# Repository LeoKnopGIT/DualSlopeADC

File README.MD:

# DualSlopeADC

Ein 12-Bit-Dual-Slope-ADC mit CH32V003 Mikrocontroller und 4-stelligem 7-Segment-Display zur Anzeige der gemessenen Gleichspannung.

## 🔧 Projektüberblick

Dieses Projekt implementiert einen Dual-Slope-Analog-Digital-Wandler (ADC), wie er z. B. in Digitalmultimetern zum Einsatz kommt. Die Schaltung misst Eingangsspannungen im Bereich von 0–3.3 V und visualisiert das Ergebnis auf einem 7-Segment-Display.

## ⚙️ Hardware

| Komponente       | Beschreibung                  |
|------------------|-------------------------------|
| Mikrocontroller  | CH32V003 (RISC-V, 48 MHz)     |
| Anzeige          | 4-stelliges 7-Segment-Display |
| Betriebsspannung | 3.3 V                         |
| Auflösung        | 12 Bit (theoretisch)          |
| Zeitauflösung    | ~20 ns (Timer mit 48 MHz)     |

## 📐 Funktionsweise

### ⏱ Prinzip: Dual-Slope-Wandlung

1. **Integration (Messphase):**  
   Eingangsspannung wird über ein RC-Glied integriert  
   → Spannungsanstieg proportional zu \( V_{in} - V_{off} \)

2. **Gegenintegration (Referenzphase):**  
   Eine konstante Referenzspannung wird integriert, bis der Ausgang wieder 0 V erreicht.

3. **Zeitmessung:**  
   Die Dauer dieser Rücklaufphase ist proportional zur Eingangsspannung.

### Simulation

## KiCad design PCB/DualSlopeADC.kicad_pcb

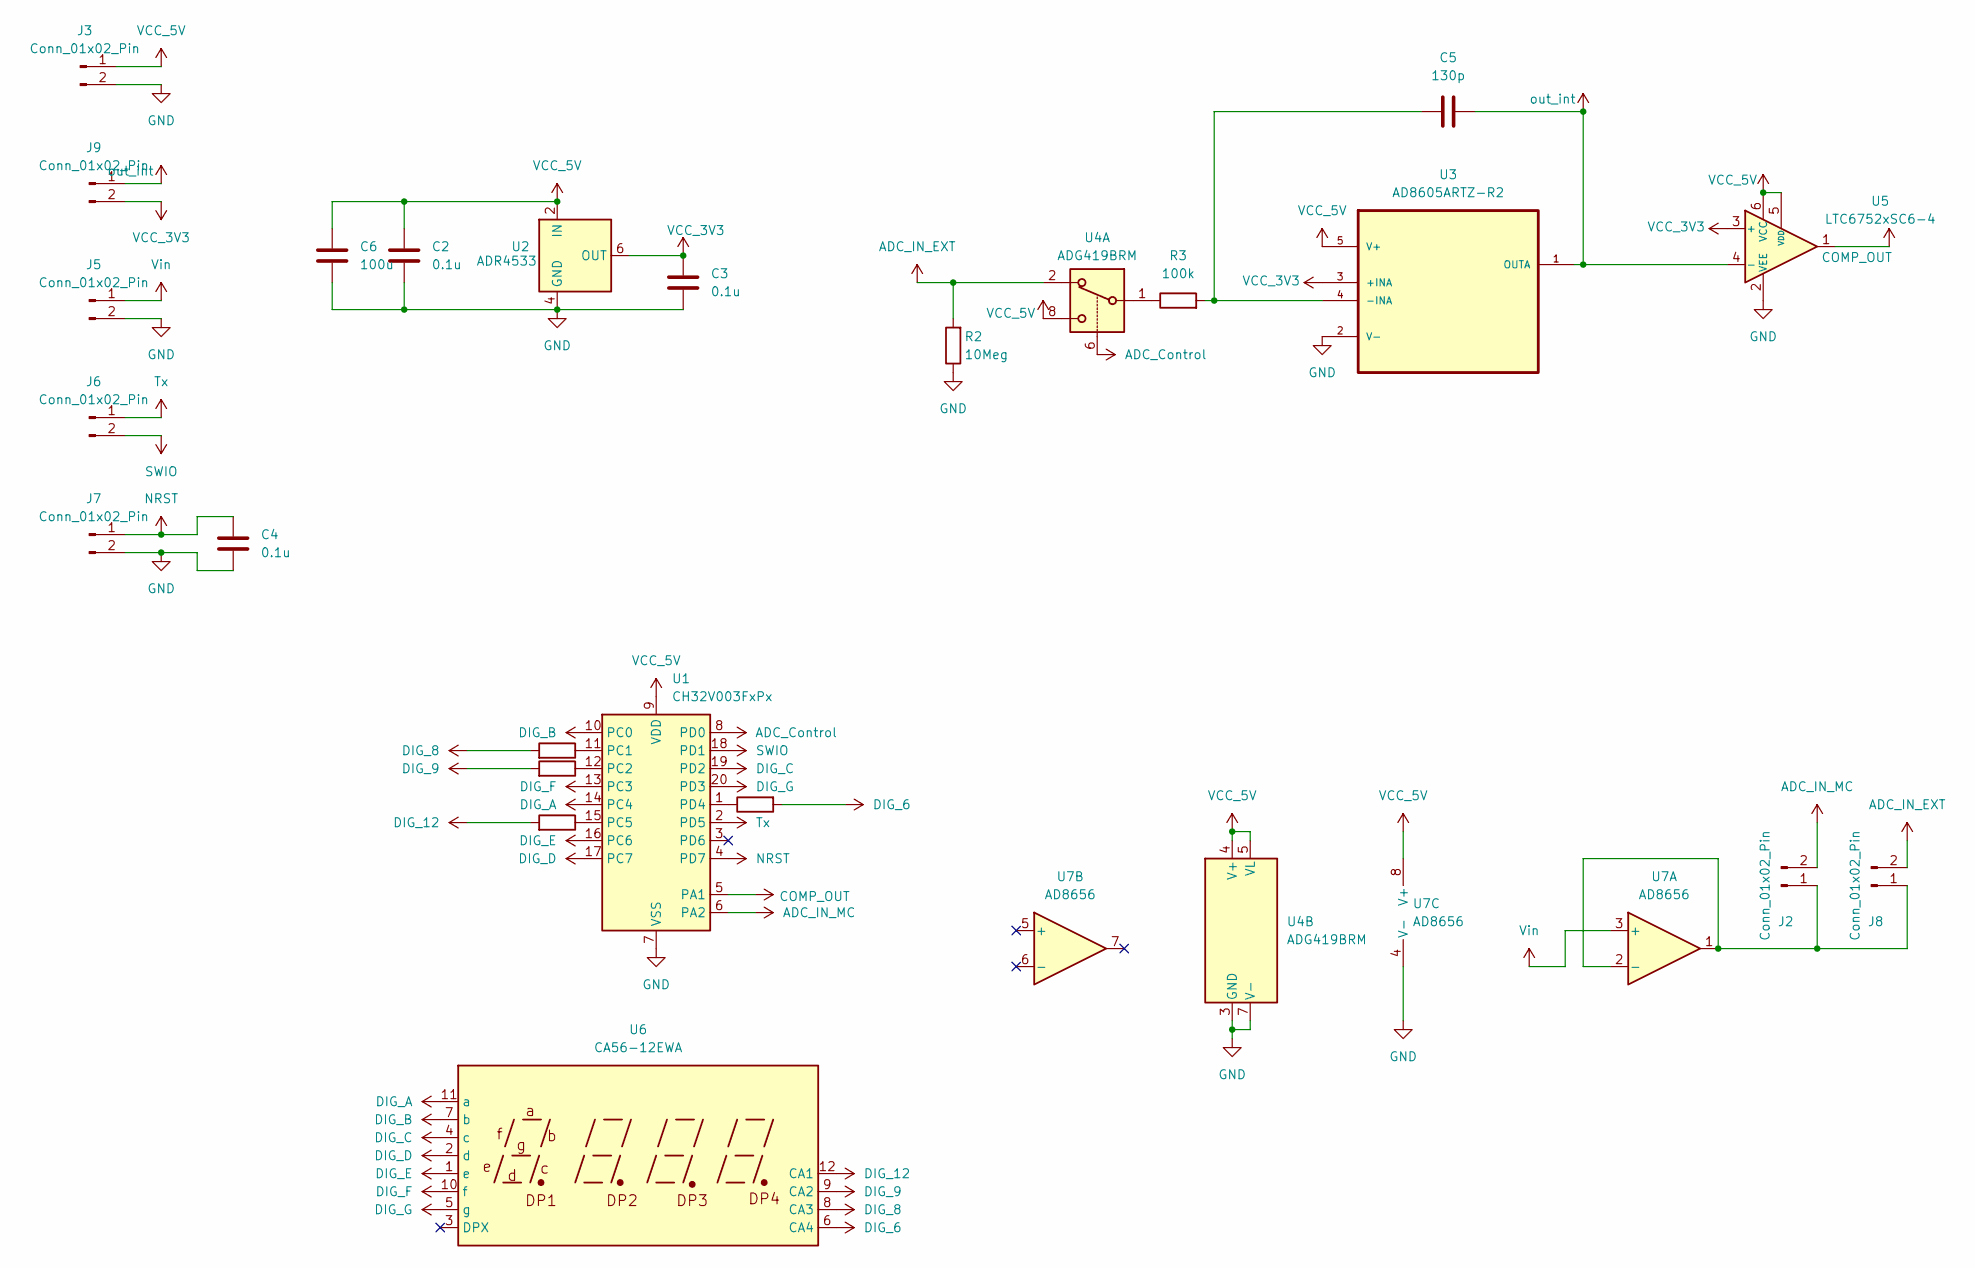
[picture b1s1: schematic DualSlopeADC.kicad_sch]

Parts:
C2, C3, C4: 0.1u; C_0805_2012Metric
C5: 130p; C_0805_2012Metric
C6: 100u; CP_Radial_D12.5mm_P5.00mm
J2, J3, J5, J6, J7, J8, J9: Conn_01x02_Pin; PinHeader_1x02_P2.54mm_Vertical
R2: 10Meg; R_0603_1608Metric
R3: 100k; R_0603_1608Metric
R4, R5, R6, R7: 330; R_0603_1608Metric
U1: CH32V003FxPx; TSSOP-20_4.4x6.5mm_P0.65mm
U2: ADR4533; SOIC-8_3.9x4.9mm_P1.27mm
U3: AD8605ARTZ-R2; SOT95P290X145-5N; MPN AD8605ARTZ-R2
U4: ADG419BRM; MSOP-8_3x3mm_P0.65mm
U5: LTC6752xSC6-4; SOT-363_SC-70-6
U6: CA56-12EWA; 3461BS_4Digit_7SegDisplay
U7: AD8656; SOIC-8_3.9x4.9mm_P1.27mm

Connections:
ADC_Control: U1.8 (PD0), U4.6
ADC_IN_EXT: J8.2, R2.2, U4.2
ADC_IN_MC: J2.2, U1.6 (PA2)
COMP_OUT: U1.5 (PA1), U5.1
DIG_6: R7.2, U6.6 (CA4)
DIG_8: R6.2, U6.8 (CA3)
DIG_9: R5.2, U6.9 (CA2)
DIG_12: R4.2, U6.12 (CA1)
DIG_A: U1.14 (PC4), U6.11 (a)
DIG_B: U1.10 (PC0), U6.7 (b)
DIG_C: U1.19 (PD2), U6.4 (c)
DIG_D: U1.17 (PC7), U6.2 (d)
DIG_E: U1.16 (PC6), U6.1 (e)
DIG_F: U1.13 (PC3), U6.10 (f)
DIG_G: U1.20 (PD3), U6.5 (g)
GND: C2.2, C3.2, C4.1, C6.2, J3.2, J5.2, J7.2, R2.1, U1.7 (VSS), U2.4 (GND), U3.2 (V-), U4.3 (GND), U4.7 (V-), U5.2 (VEE), U7.4 (V-)
NRST: C4.2, J7.1, U1.4 (PD7)
unnamed: J2.1, J8.1, U7.1, U7.2 (-)
unnamed: R3.1, U4.1
unnamed: R6.1, U1.11 (PC1)
unnamed: R5.1, U1.12 (PC2)
unnamed: R4.1, U1.15 (PC5)
unnamed: R7.1, U1.1 (PD4)
unnamed: C5.1, R3.2, U3.4 (-INA)
SWIO: J6.2, U1.18 (PD1)
Tx: J6.1, U1.2 (PD5)
VCC_3V3: C3.1, J9.2, U2.6 (OUT), U3.3 (+INA), U5.3 (+)
VCC_5V: C2.1, C6.1, J3.1, U1.9 (VDD), U2.2 (IN), U3.5 (V+), U4.4 (V+), U4.5 (VL), U4.8, U5.5 (VDD), U5.6 (VCC), U7.8 (V+)
Vin: J5.1, U7.3 (+)
out_int: C5.2, J9.1, U3.1 (OUTA), U5.4 (-)

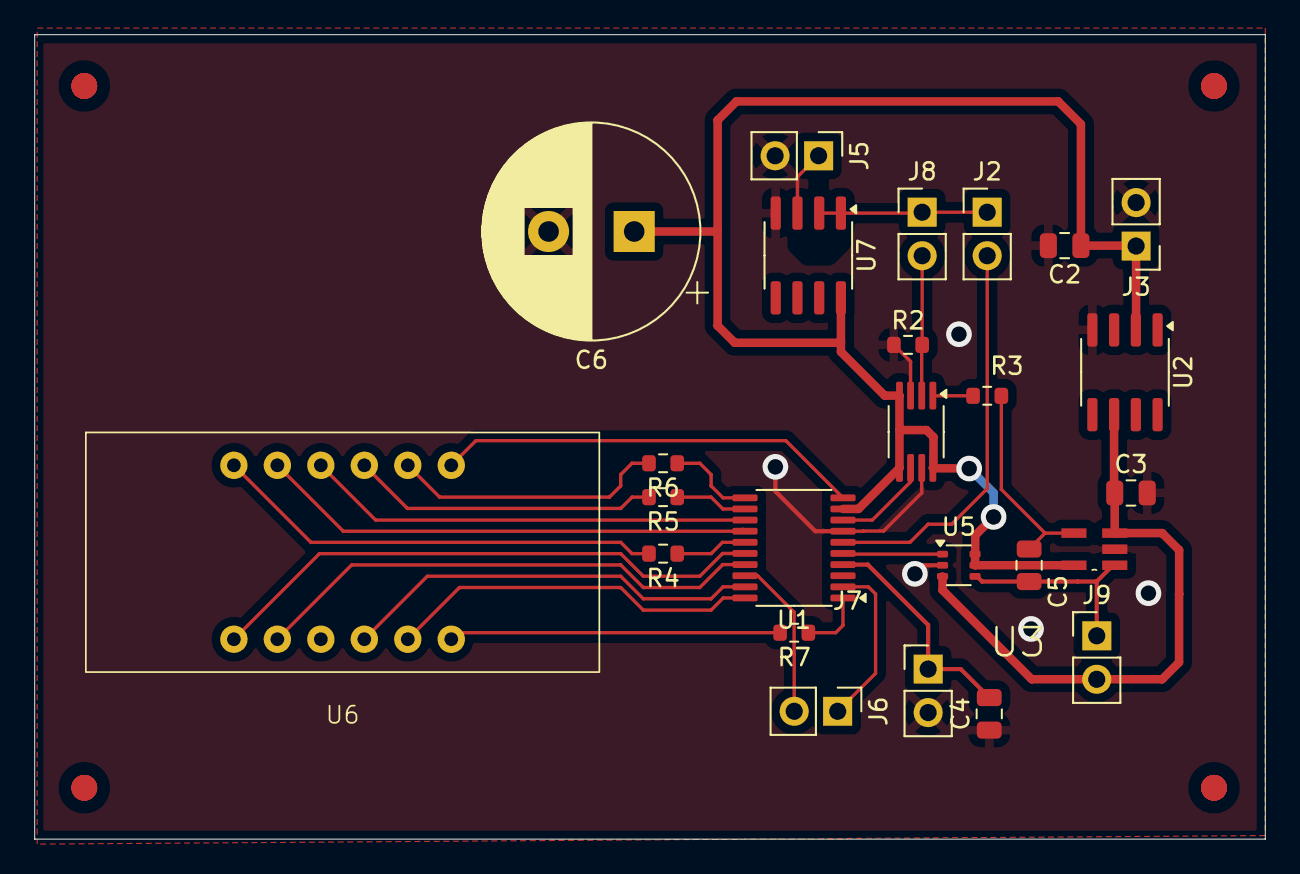
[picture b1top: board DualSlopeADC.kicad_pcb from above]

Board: 2 copper layers, 71.9 x 47.0 mm, 25 parts (0 on the bottom side), 30 nets.

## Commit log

2025-04-08 erster Entwurd ADC und Simulation
2025-04-28 KICAD
2025-04-29 out an das Entladen des Kondensators geknüpft
2025-05-05 fin2
2025-05-10 PCB design anfang
2025-05-13 CH32fun integriert
2025-05-13 Gpio mit Display und Uart funktionieren
2025-05-28 pcb weiter
2025-05-29 schaltpan fertig ohne Spannungsfolger
2025-05-30 Software inm Mounriver studio
2025-05-31 platine fertig
2025-06-04 Software ferrig, Timer einstellung auf basis das RC=100us, komplette gehirnschmelze wegen níchtlinearität durch offset sollte aber jetzt passen
2025-06-13 Fehler in pCB behoben durch OP
2025-06-24 visulle sachen
2025-06-30 doku
